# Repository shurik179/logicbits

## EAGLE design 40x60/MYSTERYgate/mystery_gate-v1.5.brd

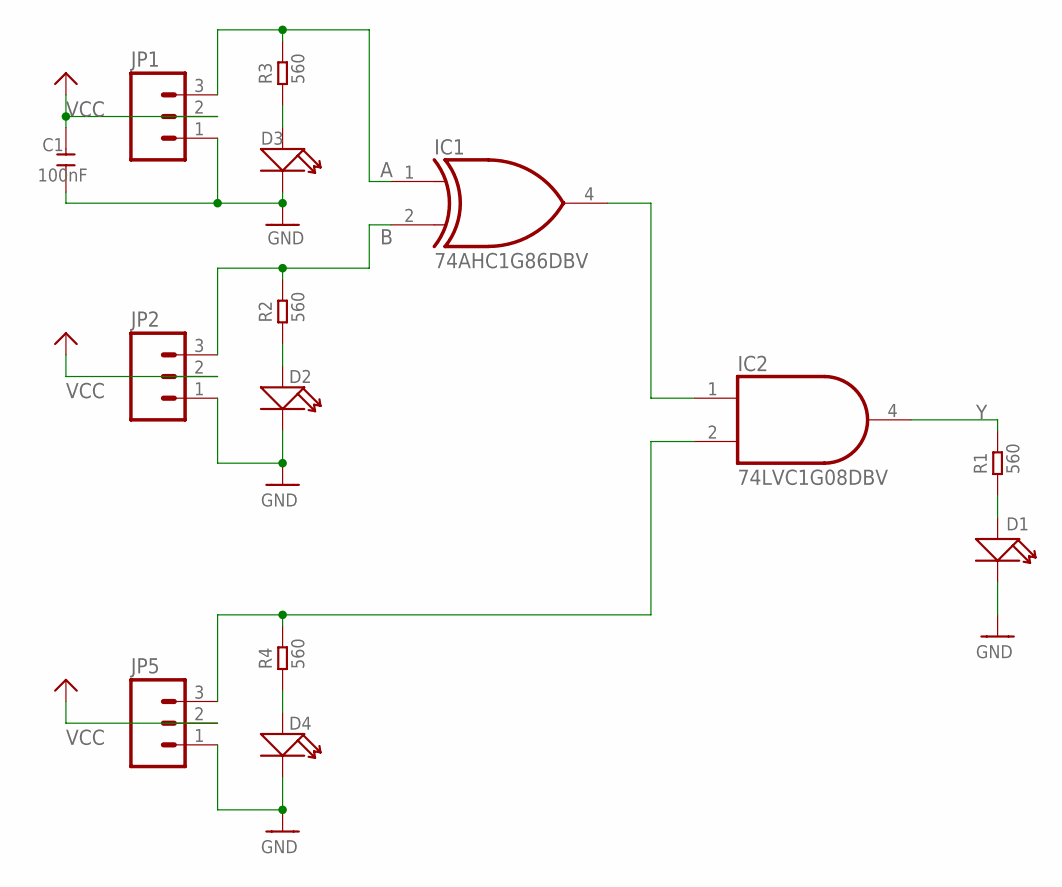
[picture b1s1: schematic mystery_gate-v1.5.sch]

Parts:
C1: 100nF; 0603
D1, D2, D3, D4: SMD-LED-0805; LED-0805
IC1: 74AHC1G86DBV; SOT23-5
IC2: 74LVC1G08DBV; SOT23-5
JP1, JP2, JP5: SPARKFUN_M031SMD-RA-MALE; SPARKFUN_1X03-SMD-MALE
R1, R2, R3, R4: 560; 0603

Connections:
A: IC1.1 (I0), JP1.3, R3.2
B: IC1.2 (I1), JP2.3, R2.2
B1: IC2.2 (I1), JP5.3, R4.2
GND: C1.1, D1.-, D2.-, D3.-, D4.-, IC1.3 (GND), IC2.3 (GND), JP1.1, JP2.1, JP5.1
unnamed: D2.+, R2.1
unnamed: D3.+, R3.1
unnamed: D1.+, R1.1
unnamed: D4.+, R4.1
unnamed: IC1.4 (O), IC2.1 (I0)
VCC: C1.2, IC1.5 (VCC), IC2.5 (VCC), JP1.2, JP2.2, JP5.2
Y: IC2.4 (O), R1.2

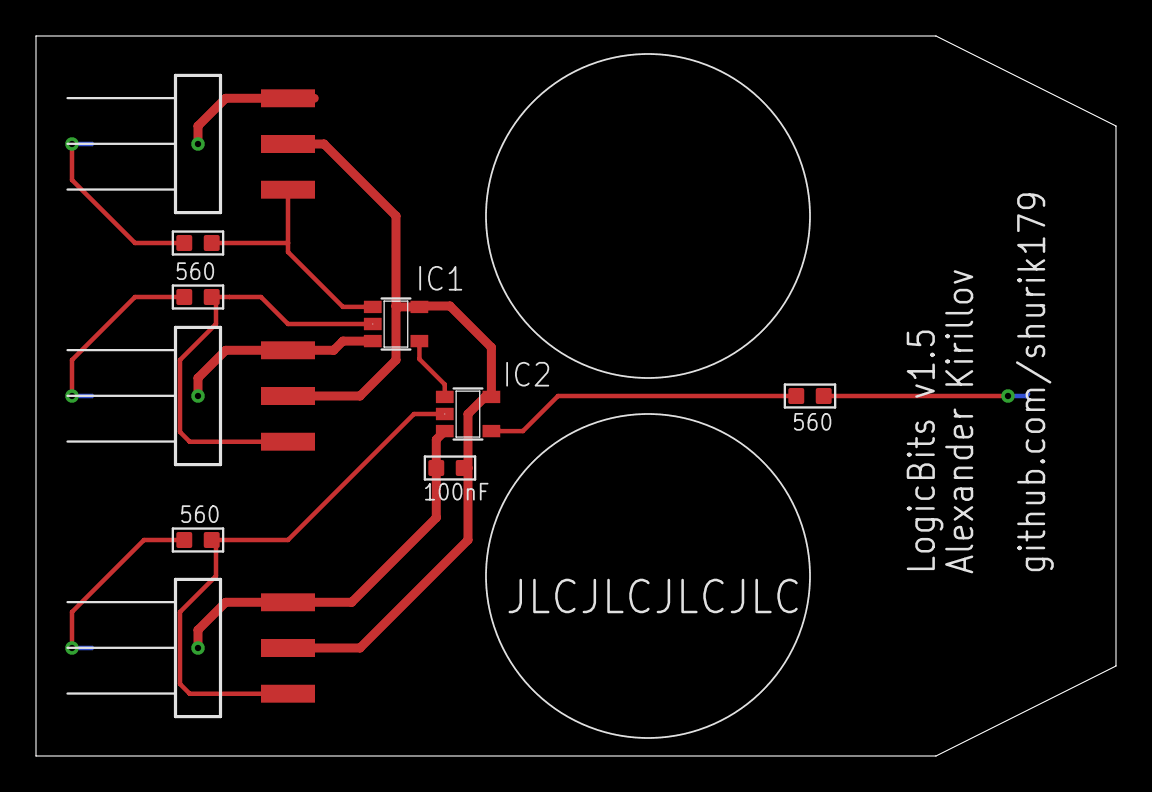
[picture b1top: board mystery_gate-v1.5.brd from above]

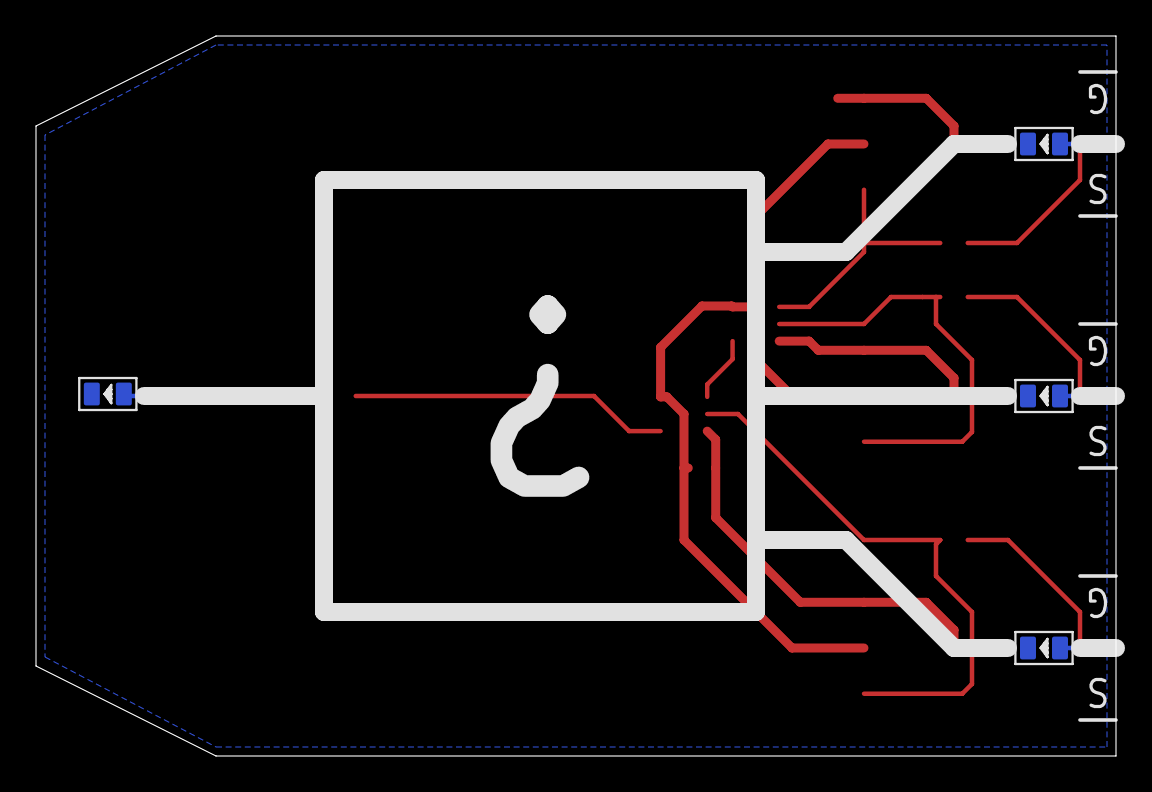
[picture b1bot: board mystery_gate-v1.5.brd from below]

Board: 2 copper layers, 60.0 x 40.0 mm, 14 parts (4 on the bottom side), 11 nets.

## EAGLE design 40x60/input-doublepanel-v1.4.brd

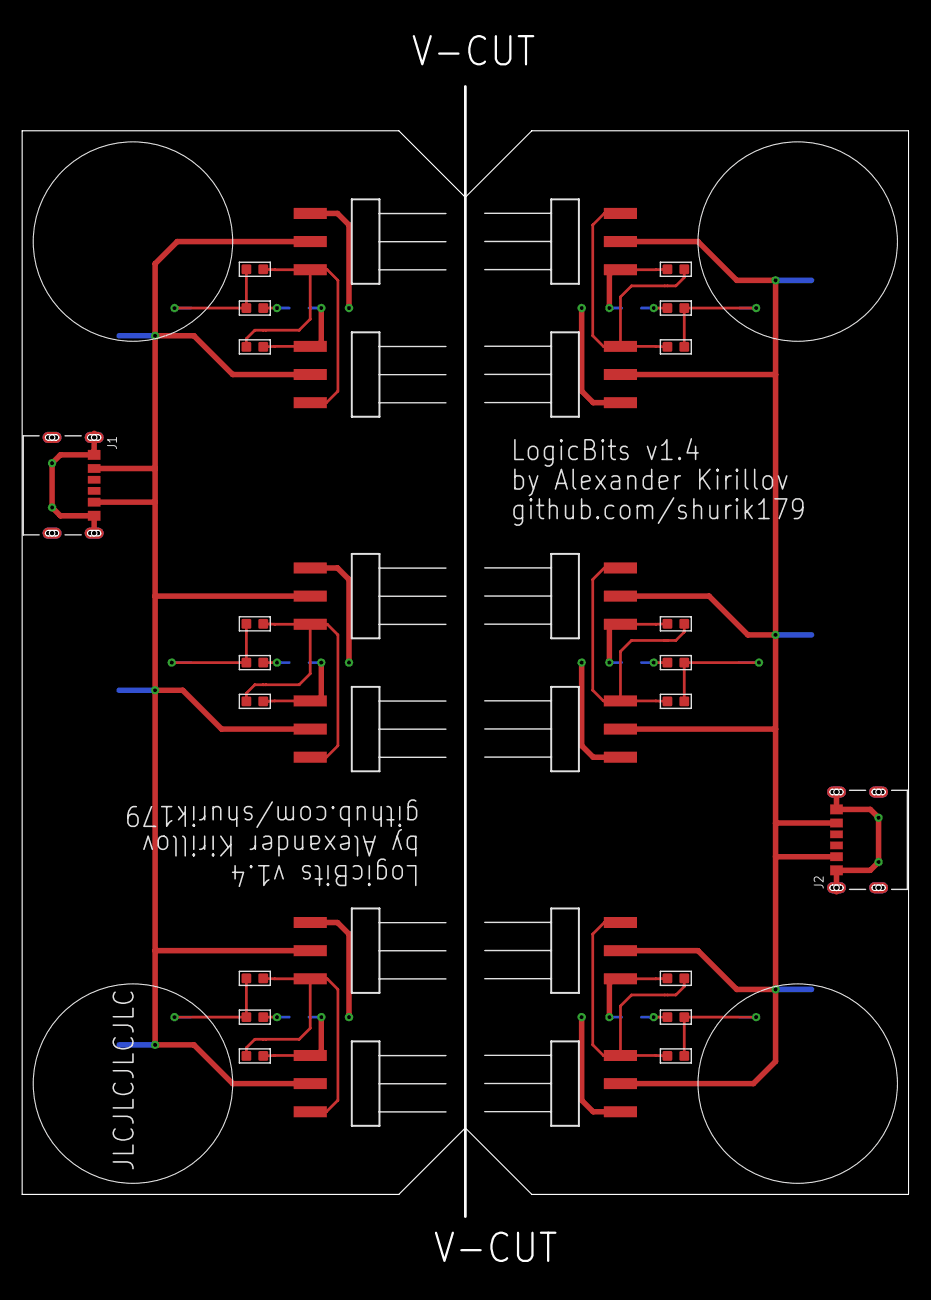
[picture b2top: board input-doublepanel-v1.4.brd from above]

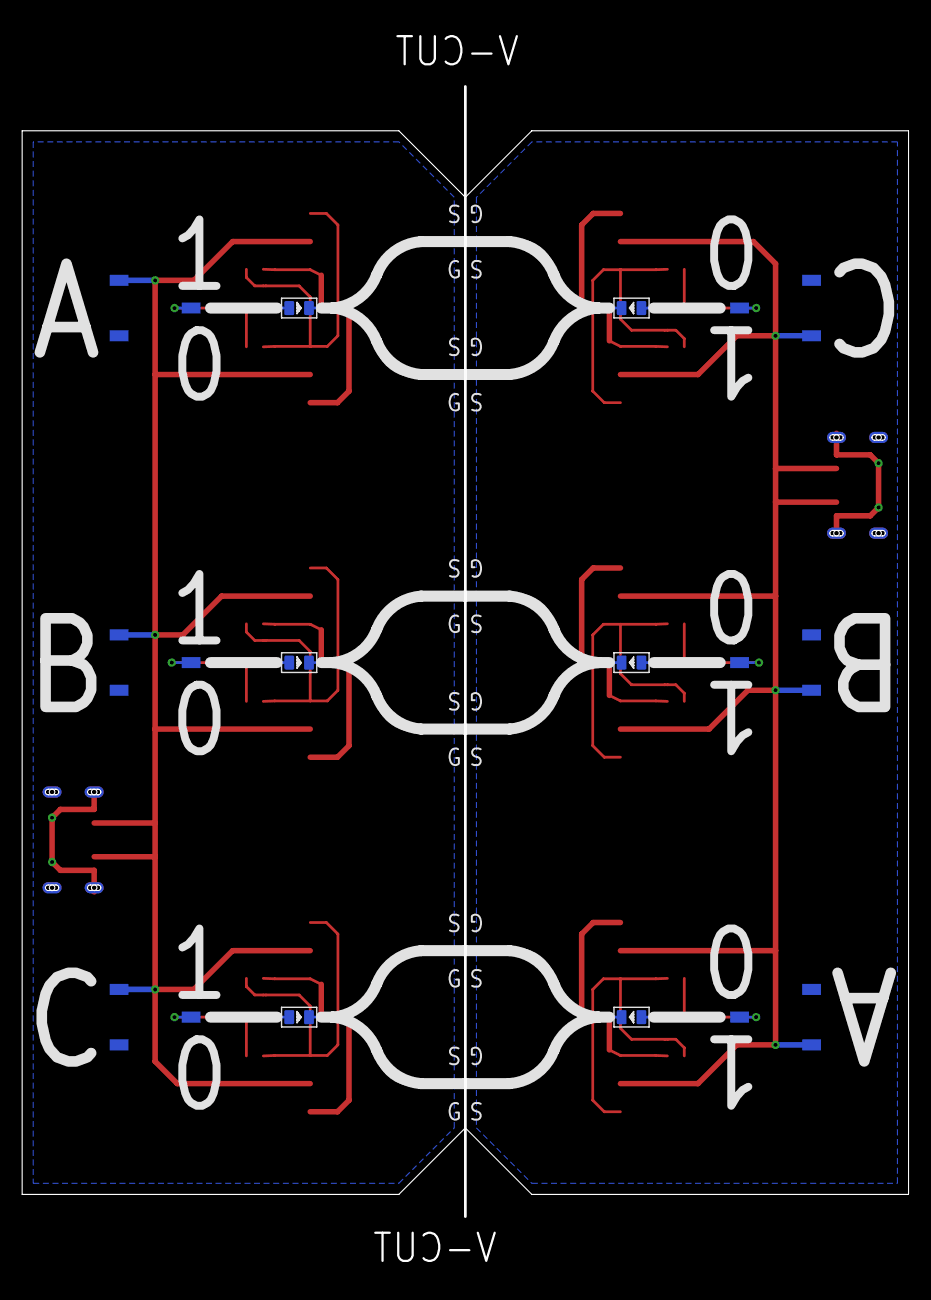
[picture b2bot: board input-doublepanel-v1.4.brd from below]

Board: 2 copper layers, 80.0 x 102.0 mm, 44 parts (12 on the bottom side), 22 nets.

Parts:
C1, C2, C3, C4, C5, C6: 1uF; 0603
D1, D2, D3, D4, D5, D6: LED-0805
J1, J2: UJC-HP-3-SMT-TR; CUI_UJC-HP-3-SMT-TR
JP1, JP2, JP3, JP4, JP5, JP6, JP7, JP8, JP9, JP10, JP11, JP12: SPARKFUN_1X03-SMD-MALE
R1, R3, R5, R7, R9, R11: 560; 0603
R2, R4, R6, R8, R10, R12: 220; 0603
U$1, U$2, U$3, U$4, U$6, U$8: SWITCH-K3-1235S

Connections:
GND: C1.1, C2.1, C3.1, D2.-, D3.-, D4.-, J1.A12, J1.B12, J1.S1, J1.S2, J1.S3, J1.S4, JP3.3, JP4.3, JP5.3, JP6.3, JP7.3, JP8.3, U$4.P$3, U$6.P$3, U$8.P$3
GND1: C4.1, C5.1, C6.1, D1.-, D5.-, D6.-, J2.A12, J2.B12, J2.S1, J2.S2, J2.S3, J2.S4, JP1.3, JP2.3, JP9.3, JP10.3, JP11.3, JP12.3, U$1.P$3, U$2.P$3, U$3.P$3
unnamed: R1.2, R2.2, U$4.P$2
unnamed: R3.2, R4.2, U$6.P$2
unnamed: R5.2, R6.2, U$8.P$2
unnamed: D3.+, R3.1
unnamed: D2.+, R1.1
unnamed: D4.+, R5.1
unnamed: R7.2, R8.2, U$1.P$2
unnamed: R9.2, R10.2, U$2.P$2
unnamed: R11.2, R12.2, U$3.P$2
unnamed: D5.+, R9.1
unnamed: D1.+, R7.1
unnamed: D6.+, R11.1
SIGNAL1: C1.2, JP3.1, JP4.1, R2.1
SIGNAL2: C2.2, JP5.1, JP6.1, R4.1
SIGNAL3: C3.2, JP7.1, JP8.1, R6.1
SIGNAL4: C4.2, JP1.1, JP2.1, R8.1
SIGNAL5: C5.2, JP9.1, JP10.1, R10.1
SIGNAL6: C6.2, JP11.1, JP12.1, R12.1
VCC: J1.A9, J1.B9, JP3.2, JP4.2, JP5.2, JP6.2, JP7.2, JP8.2, U$4.P$1, U$6.P$1, U$8.P$1
VCC1: J2.A9, J2.B9, JP1.2, JP2.2, JP9.2, JP10.2, JP11.2, JP12.2, U$1.P$1, U$2.P$1, U$3.P$1
